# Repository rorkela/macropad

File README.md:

# EE2504: Hybrid Macropad (Wired + Dongle)

## Team

| Name | Roll Number |
|---|---|
| Sarthak Kumar Mishra |EE24BTECH11221|
| Naman Singh |EE24BTECH11216|
| Dhawal Saini |EE24BTECH11015|
| Sidharth V |EE24BTECH11224|
| Vantaku Sai Yashwant |EE24BTECH11225|
| Sriram Nulu |EE24BTECH11217|

## Details
- 2 Layer PCB for Macropad+Dongle Pair
- STM32F103C8T6 Based
- Programmed with `libopencm3`
- ssd1306 display integrated
- CAD Model designed to be 3D Printed for keycaps, encoder caps and casing.
- `microui` based key-map programming interface

## Instruction
1. Make the libraries (`libopencm3`)
2. Make and flash bootloader using `make flash`
3. Make and flash macropad firmware using `make flash` or the dfu script
4. Generate keymaps and flash using `mapping_gen`
# Current Status
- [x] PCB Ordered
## Wired
- [x] Bootloader Firmware
- [x] USB HID Firmware
- [x] DFU Firmware
- [x] Encoder Firmware
- [x] Display Firmware
- [x] All module integration
- [x] Multi key mapping
- [ ] Multi key sequential mapping

## Wireless
- [x] Dongle testing
- [x] nRF24L01 Firmware
- [ ] Battery Charging check
- [ ] Soldering SMD Mosfet + nRF modules
- [ ] Replacing PROG resistor for TP4056 module
- [ ] Complete Integration
## Other
- [x] Mapping generation and flashing with DFU
- [x] GUI
- [ ] Size Optimization for keymaps

## Images

## Links
- [CAD Model (Onshape)](https://cad.onshape.com/documents/8695aacad1c4b6aaf32709eb/w/c4719be3eaa84105acadf71a/e/89d918a88e3d346d4846fa41)

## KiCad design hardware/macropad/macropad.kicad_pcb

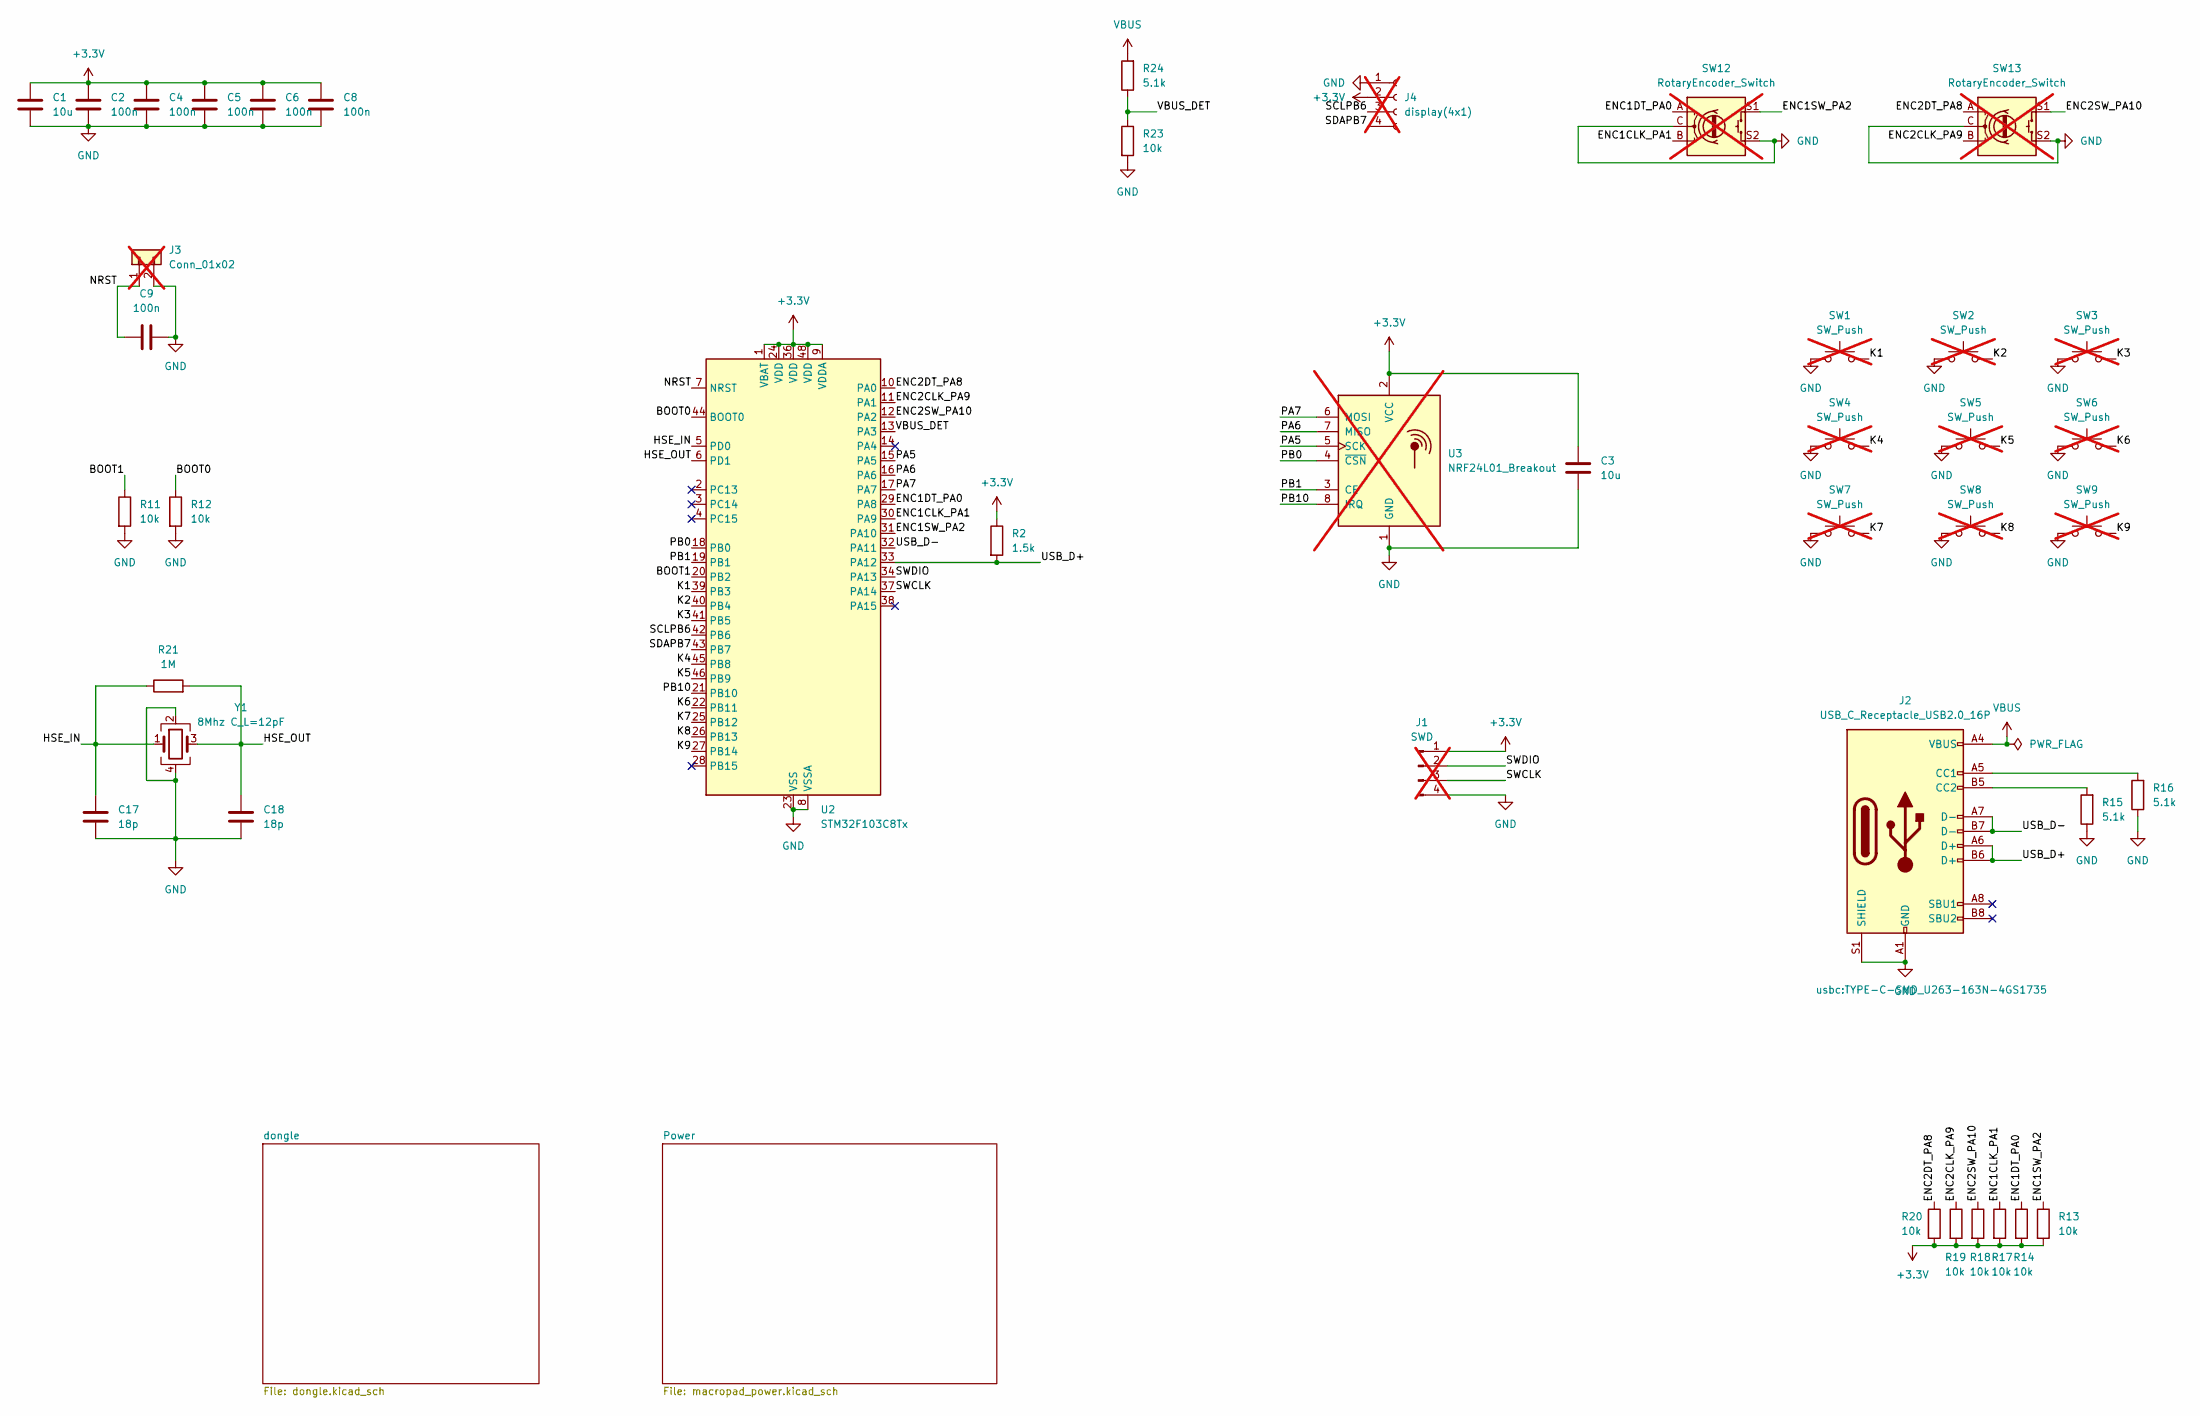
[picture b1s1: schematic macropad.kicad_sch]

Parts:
C1, C3: 10u; C_0805_2012Metric
C2, C4, C5, C6, C8, C9: 100n; C_0603_1608Metric
C17: 18p; C_0201_0603Metric
C18: 18p; C_0201_0603Metric; MPN GCM0335C1H180FA16D
J1: SWD; PinHeader_1x04_P2.54mm_Vertical; not fitted
J2: USB_C_Receptacle_USB2.0_16P; TYPE-C-SMD_U263-163N-4GS1735; MPN U263-163N-4WS1735-XKB-5A
J3: Conn_01x02; Hirose_DF13-02P-1.25DSA_1x02_P1.25mm_Vertical; not fitted
J4: display(4x1); PinHeader_1x04_P2.54mm_Vertical; not fitted
R2: 1.5k; R_0603_1608Metric
R11, R12, R14, R17, R18, R19, R20, R23: 10k; R_0805_2012Metric
R13: 10k; R_0805_2012Metric; MPN RC0805JR-0710KL
R15: 5.1k; R_0603_1608Metric; MPN RT0603FRE075K1L
R16, R24: 5.1k; R_0603_1608Metric
R21: 1M; R_0603_1608Metric
SW1, SW2, SW3, SW4, SW5, SW6, SW7, SW8, SW9: SW_Push; Kailh_socket_MX; not fitted
SW12: RotaryEncoder_Switch; RotaryEncoder_Alps_EC12E-Switch_Vertical_H20mm; MPN KY-040; not fitted
SW13: RotaryEncoder_Switch; RotaryEncoder_Alps_EC12E-Switch_Vertical_H20mm; not fitted
U2: STM32F103C8Tx; LQFP-48_7x7mm_P0.5mm; MPN STM32F103C8T6
U3: NRF24L01_Breakout; nRF24L01_Breakout; not fitted
Y1: 8Mhz C_L=12pF; Crystal_SMD_3225-4Pin_3.2x2.5mm; MPN X32258MOB4SI

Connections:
+3.3V: C1.1, C2.1, C3.1, C4.1, C5.1, C6.1, C8.1, J1.1, J4.2, R2.1, R13.2, R14.2, R17.2, R18.2, R19.2, R20.2, U2.1 (VBAT), U2.9 (VDDA), U2.24 (VDD), U2.36 (VDD), U2.48 (VDD), U3.2 (VCC); also elsewhere on the board
/BOOT0: R12.1, U2.44 (BOOT0)
/BOOT1: R11.1, U2.20 (PB2)
/ENC1CLK_PA1: R17.1, SW12.B, U2.30 (PA9)
/ENC1DT_PA0: R14.1, SW12.A, U2.29 (PA8)
/ENC1SW_PA2: R13.1, SW12.S1, U2.31 (PA10)
/ENC2CLK_PA9: R19.1, SW13.B, U2.11 (PA1)
/ENC2DT_PA8: R20.1, SW13.A, U2.10 (PA0)
/ENC2SW_PA10: R18.1, SW13.S1, U2.12 (PA2)
/HSE_IN: C17.1, R21.1, U2.5 (PD0), Y1.1
/HSE_OUT: C18.1, R21.2, U2.6 (PD1), Y1.3
/K1: SW1.2, U2.39 (PB3)
/K2: SW2.2, U2.40 (PB4)
/K3: SW3.2, U2.41 (PB5)
/K4: SW4.2, U2.45 (PB8)
/K5: SW5.2, U2.46 (PB9)
/K6: SW6.2, U2.22 (PB11)
/K7: SW7.2, U2.25 (PB12)
/K8: SW8.2, U2.26 (PB13)
/K9: SW9.2, U2.27 (PB14)
/NRST: C9.2, J3.1, U2.7 (NRST)
/PA5: U2.15 (PA5), U3.5 (SCK)
/PA6: U2.16 (PA6), U3.7 (MISO)
/PA7: U2.17 (PA7), U3.6 (MOSI)
/PB0: U2.18 (PB0), U3.4 (~CSN)
/PB1: U2.19 (PB1), U3.3 (CE)
/PB10: U2.21 (PB10), U3.8 (IRQ)
/SCLPB6: J4.3, U2.42 (PB6)
/SDAPB7: J4.4, U2.43 (PB7)
/SWCLK: J1.3, U2.37 (PA14)
/SWDIO: J1.2, U2.34 (PA13)
/USB_D+: J2.A6 (D+), J2.B6 (D+), R2.2, U2.33 (PA12)
/USB_D-: J2.A7 (D-), J2.B7 (D-), U2.32 (PA11)
/VBUS_DET: R23.1, R24.1, U2.13 (PA3)
GND: C1.2, C2.2, C3.2, C4.2, C5.2, C6.2, C8.2, C9.1, C17.2, C18.2, J1.4, J2.A1 (GND), J2.A12 (GND), J2.B1 (GND), J2.B12 (GND), J2.S1 (SHIELD), J3.2, J4.1, R11.2, R12.2, R15.1, R16.1, R23.2, SW1.1, SW2.1, SW3.1, SW4.1, SW5.1, SW6.1, SW7.1, SW8.1, SW9.1, SW12.C, SW12.S2, SW13.C, SW13.S2, U2.8 (VSSA), U2.23 (VSS), U2.35 (VSS), U2.47 (VSS), U3.1 (GND), Y1.2, Y1.4; also elsewhere on the board
unnamed: J2.A5 (CC1), R16.2
unnamed: J2.B5 (CC2), R15.2
VBUS: J2.A4 (VBUS), J2.A9 (VBUS), J2.B4 (VBUS), J2.B9 (VBUS), R24.2; also elsewhere on the board

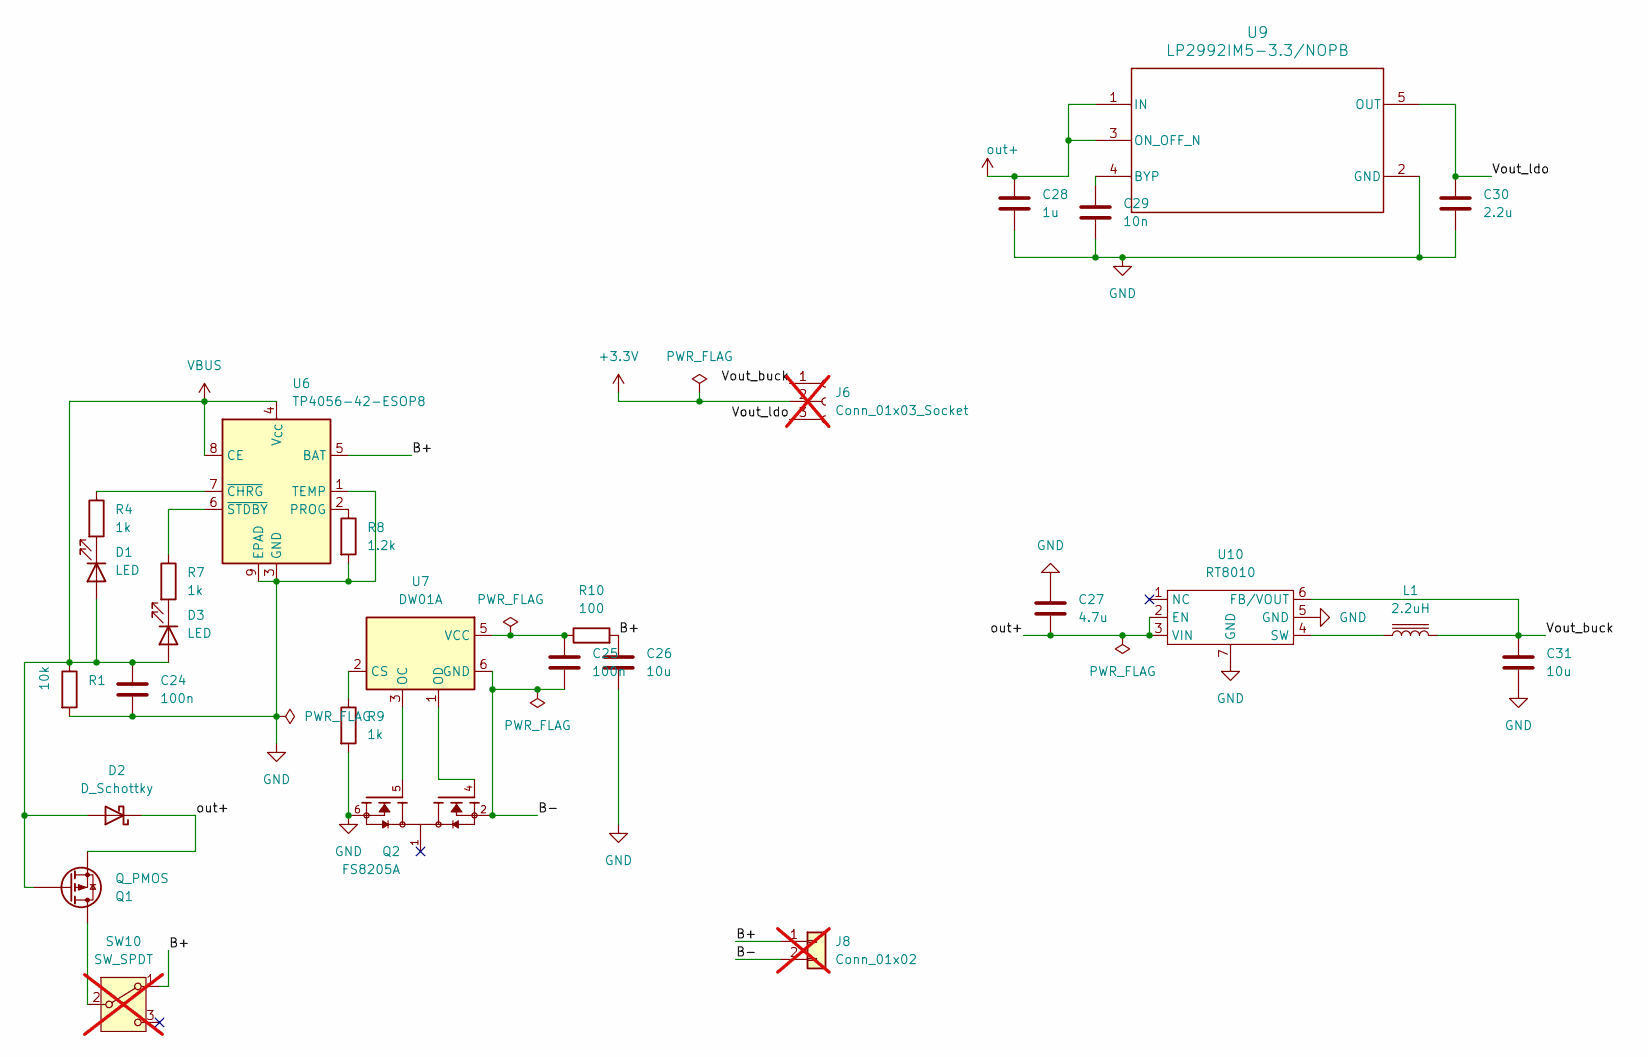
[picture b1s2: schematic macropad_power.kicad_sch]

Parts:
C24: 100n; C_0603_1608Metric; MPN AC0603JRX7R9BB104
C25: 100n; C_0603_1608Metric
C26: 10u; C_0805_2012Metric; MPN GRT21BR61C106KE01L
C27: 4.7u; C_0603_1608Metric; MPN GRM188Z71C475KE21D
C28: 1u; C_0805_2012Metric
C29: 10n; C_0603_1608Metric
C30: 2.2u; C_0603_1608Metric; MPN TMK107BBJ225KAHT
C31: 10u; C_0805_2012Metric
D1: LED; LED_0805_2012Metric
D2: D_Schottky; D_SMA; MPN SS34
D3: LED; LED_0805_2012Metric; MPN 17-21SURC/S530-A3/4T
J6: Conn_01x03_Socket; Hirose_DF13-03P-1.25DSA_1x03_P1.25mm_Vertical; not fitted
J8: Conn_01x02; SolderWire-0.5sqmm_1x02_P4.6mm_D0.9mm_OD2.1mm; not fitted
L1: 2.2uH; L_10.4x10.4_H4.8; MPN CDRH104R 2.2uH
Q1: Q_PMOS; SOT-23-3; MPN SI2305CDS-T1-GE3
Q2: FS8205A; SOP65P640X120-8N; PARTREV 1.7
R1: 10k; R_0805_2012Metric
R4, R7: 1k; R_0603_1608Metric
R8: 1.2k; R_0603_1608Metric; MPN AC0603FR-071K2L
R9: 1k; R_0603_1608Metric; MPN AC0603FR-071KL
R10: 100; R_0201_0603Metric; MPN AC0201FR-07100RL
SW10: SW_SPDT; SS12F23L5 spdt; not fitted
U6: TP4056-42-ESOP8; SOIC-8-1EP_3.9x4.9mm_P1.27mm_EP2.41x3.3mm_ThermalVias; MPN TP4056
U7: DW01A; SOT-23-6; MPN DW01A
U9: LP2992IM5-3.3/NOPB; DBV0005A_N; MPN LP2992IM5-3.3/NOPB
U10: RT8010; WDFN-6L; MPN RT8010-33GQW

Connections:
+3.3V: J6.2; also elsewhere on the board
/Power/B+: C26.1, J8.1, R10.2, SW10.1 (A), U6.5 (BAT)
/Power/B-: C25.2, J8.2, Q2.2, Q2.3, U7.6 (GND)
/Power/Vout_buck: C31.1, J6.1, L1.2, U10.6 (FB/VOUT)
/Power/Vout_ldo: C30.1, J6.3, U9.5 (OUT)
GND: C24.2, C26.2, C27.1, C28.2, C29.2, C30.2, C31.2, Q2.6, Q2.7, R1.2, R8.2, R9.2, U6.1 (TEMP), U6.3 (GND), U6.9 (EPAD), U9.2 (GND), U10.5 (GND), U10.7 (GND); also elsewhere on the board
unnamed: D1.1 (K), R4.2
unnamed: D3.1 (K), R7.2
unnamed: Q1.3 (D), SW10.2 (B)
unnamed: R8.1, U6.2 (PROG)
unnamed: R4.1, U6.7 (~CHRG)
unnamed: R7.1, U6.6 (~STDBY)
unnamed: R9.1, U7.2 (CS)
unnamed: Q2.5, U7.3 (OC)
unnamed: Q2.4, U7.1 (OD)
unnamed: C25.1, R10.1, U7.5 (VCC)
unnamed: C29.1, U9.4 (BYP)
unnamed: L1.1, U10.4 (SW)
VBUS: C24.1, D1.2 (A), D2.2 (A), D3.2 (A), Q1.1 (G), R1.1, U6.4 (V_{CC}), U6.8 (CE); also elsewhere on the board
out+: C27.2, C28.1, D2.1 (K), Q1.2 (S), U9.1 (IN), U9.3 (ON_OFF_N), U10.2 (EN), U10.3 (VIN)

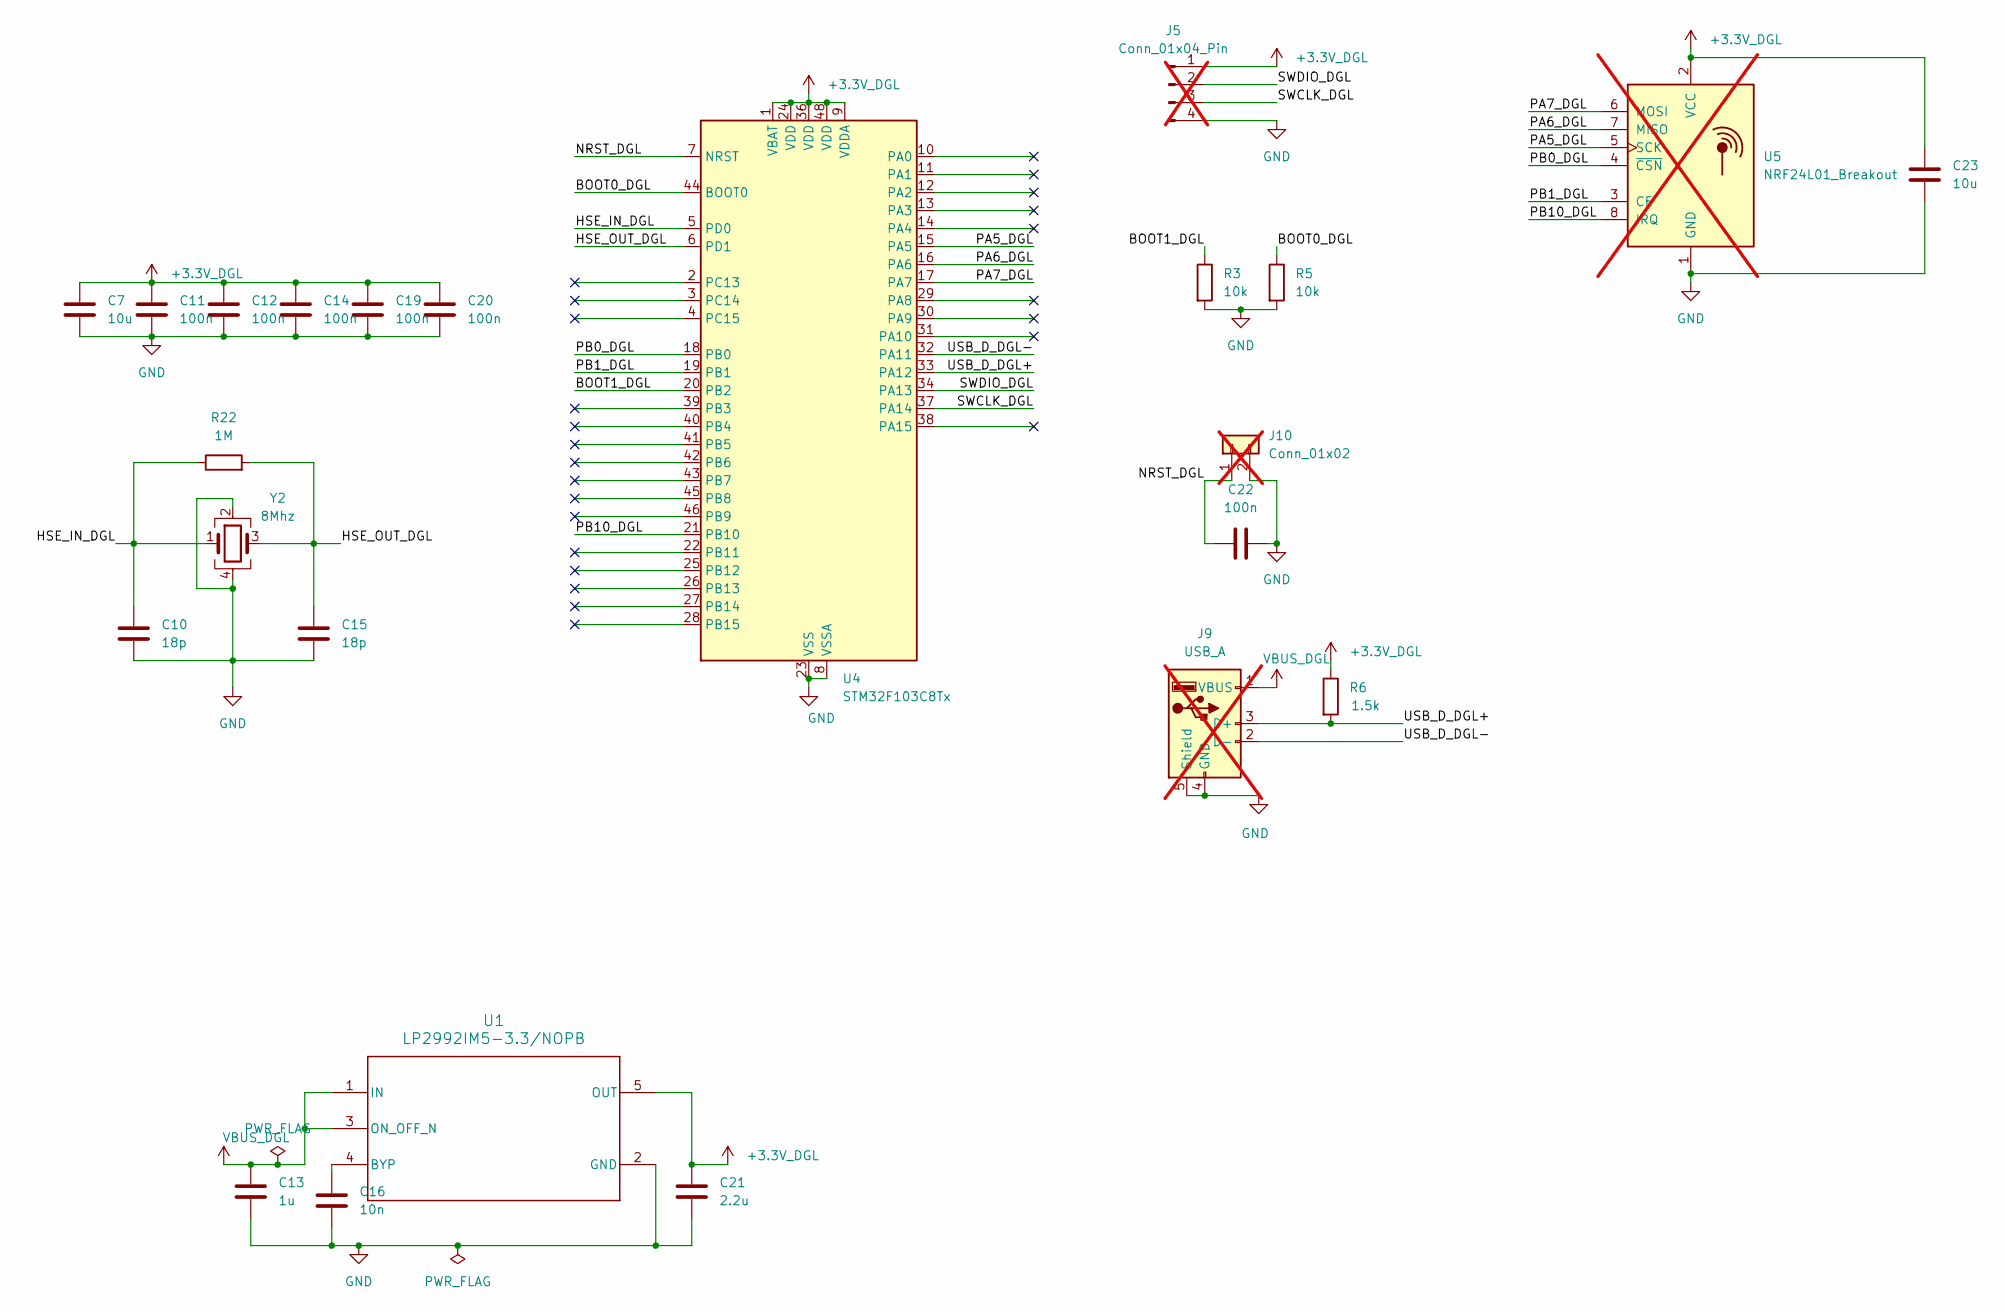
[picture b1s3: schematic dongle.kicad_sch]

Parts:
C7, C23: 10u; C_0805_2012Metric
C10, C15: 18p; C_0201_0603Metric
C11, C12, C14, C19, C20, C22: 100n; C_0603_1608Metric
C13: 1u; C_0805_2012Metric; MPN UMK212B7105KGHT
C16: 10n; C_0603_1608Metric
C21: 2.2u; C_0603_1608Metric
J5: Conn_01x04_Pin; PinHeader_1x04_P2.54mm_Horizontal; not fitted
J9: USB_A; U-G-O4DD-W-1; not fitted
J10: Conn_01x02; Hirose_DF13-02P-1.25DSA_1x02_P1.25mm_Vertical; not fitted
R3, R5: 10k; R_0805_2012Metric
R6: 1.5k; R_0603_1608Metric; MPN RT0603FRE071K5L
R22: 1M; R_0603_1608Metric; MPN CRCW06031M00FKEA
U1: LP2992IM5-3.3/NOPB; DBV0005A_N
U4: STM32F103C8Tx; LQFP-48_7x7mm_P0.5mm
U5: NRF24L01_Breakout; nRF24L01_Breakout; not fitted
Y2: 8Mhz; Crystal_SMD_3225-4Pin_3.2x2.5mm; MPN X32258MOB4SI

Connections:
+3.3V_DGL: C7.1, C11.1, C12.1, C14.1, C19.1, C20.1, C21.1, C23.1, J5.1, R6.1, U1.5 (OUT), U4.1 (VBAT), U4.9 (VDDA), U4.24 (VDD), U4.36 (VDD), U4.48 (VDD), U5.2 (VCC)
/dongle/BOOT0_DGL: R5.1, U4.44 (BOOT0)
/dongle/BOOT1_DGL: R3.1, U4.20 (PB2)
/dongle/HSE_IN_DGL: C10.1, R22.1, U4.5 (PD0), Y2.1
/dongle/HSE_OUT_DGL: C15.1, R22.2, U4.6 (PD1), Y2.3
/dongle/NRST_DGL: C22.2, J10.1, U4.7 (NRST)
/dongle/PA5_DGL: U4.15 (PA5), U5.5 (SCK)
/dongle/PA6_DGL: U4.16 (PA6), U5.7 (MISO)
/dongle/PA7_DGL: U4.17 (PA7), U5.6 (MOSI)
/dongle/PB0_DGL: U4.18 (PB0), U5.4 (~CSN)
/dongle/PB1_DGL: U4.19 (PB1), U5.3 (CE)
/dongle/PB10_DGL: U4.21 (PB10), U5.8 (IRQ)
/dongle/SWCLK_DGL: J5.3, U4.37 (PA14)
/dongle/SWDIO_DGL: J5.2, U4.34 (PA13)
/dongle/USB_D_DGL+: J9.3 (D+), R6.2, U4.33 (PA12)
/dongle/USB_D_DGL-: J9.2 (D-), U4.32 (PA11)
GND: C7.2, C10.2, C11.2, C12.2, C13.2, C14.2, C15.2, C16.2, C19.2, C20.2, C21.2, C22.1, C23.2, J5.4, J9.4 (GND), J9.5 (Shield), J10.2, R3.2, R5.2, U1.2 (GND), U4.8 (VSSA), U4.23 (VSS), U4.35 (VSS), U4.47 (VSS), U5.1 (GND), Y2.2, Y2.4; also elsewhere on the board
unnamed: C16.1, U1.4 (BYP)
VBUS_DGL: C13.1, J9.1 (VBUS), U1.1 (IN), U1.3 (ON_OFF_N)

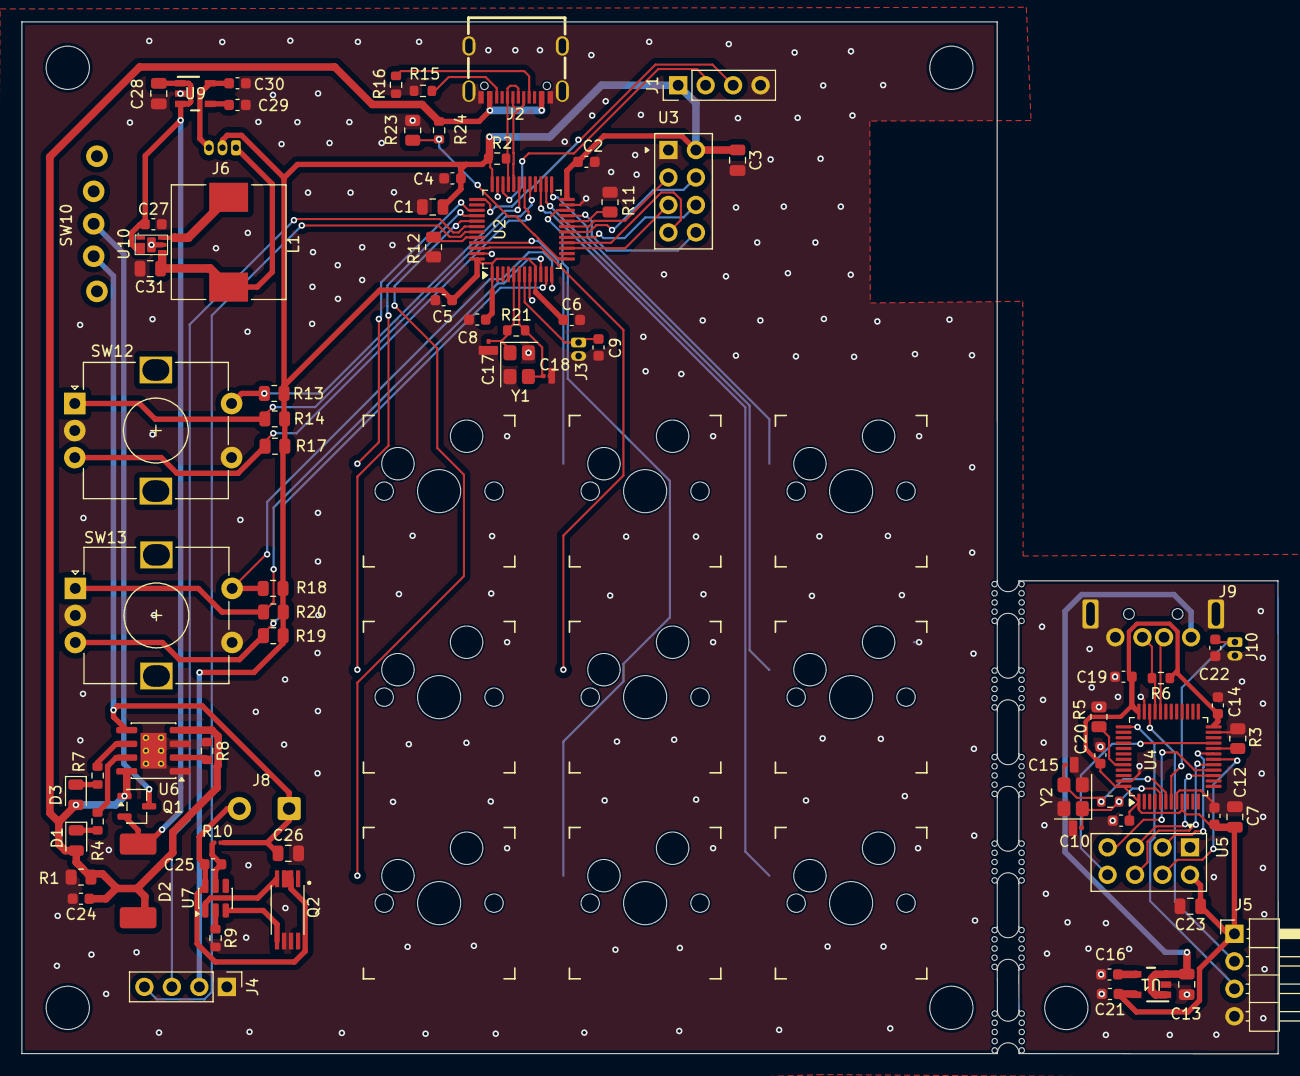
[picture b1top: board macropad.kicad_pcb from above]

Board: 2 copper layers, 116.1 x 95.4 mm, 93 parts (1 on the bottom side), 73 nets.

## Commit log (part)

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2026-02-18 init push
2026-02-25 push
2026-02-26 added some things like power
2026-02-26 peripherals connected passive,keys still to be done
2026-02-26 added firmware, gitignore; removed dongle kicad project
2026-02-26 removed .gitmodules
2026-02-26 switches added. folders deleted
2026-02-26 switches fixed
2026-02-26 added reset and 3x2 connector
2026-02-27 schema added for dongle. rearranged some parts
2026-02-27 schematic halfass done
2026-02-28 updated gitignore
2026-02-28 ERC satisfied. Net names changed for not global
2026-02-28 updated rules.mk
2026-02-28 added code for testing internal pullup
2026-02-28 removed keyswitch pullups
2026-02-28 switched to usb-c receptacle
2026-02-28 added new sch
2026-02-28 moved powering circuitry to new schematic
2026-02-28 captured TP4056 module
2026-02-28 captured the Buck(3_3V)
2026-03-01 added debouncing caps
2026-03-01 added 1k resistors to leds
2026-03-01 changed load capacitance, added oscillator for pad
2026-03-01 update oscillator + passives'
2026-03-01 something changed. i didnt track
2026-03-02 updated footprints
2026-03-03 replaced enc with module
2026-03-03 updated bat switch, added 10k resistors. fixed fps
2026-03-03 updated lp2992
2026-03-04 added usb-c receptacle footprint
2026-03-04 updated symbols. changed power. erc fixxed halfway
2026-03-05 erc for power checked
2026-03-05 erc for macropad checked
2026-03-05 updated symbols. all erc passed
2026-03-05 added usba fp, updated pcb, 5v to vbus
2026-03-06 replaced buttons with pads
2026-03-06 updated usb-c receptacle footprint
2026-03-11 updated. comments in whatsapp
2026-03-12 SS12F23L5 foorpting added
2026-03-12 updated pcb with switch
2026-03-12 pcb macropad done
2026-03-12 pcb done
2026-03-16 Updated Layout
2026-03-18 wrote code for testing i2c with ssd1306
2026-03-18 updated schematic and drc
2026-03-18 Macropad layout kinda done
2026-03-19 added drc
2026-03-19 routing
2026-03-19 rt8010 footprint
2026-03-19 rt8010 footprint+symbol done
2026-03-19 routing phase 2
2026-03-22 routing-macropad(67)
2026-03-26 updated dongle
2026-03-26 0-DRC
2026-03-29 0drc
2026-04-01 changes made
2026-04-01 schottkey updated and added mount hole
2026-04-02 added single pad usbc footprint
2026-04-02 added hole
2026-04-04 stitching done
2026-04-06 fab outputs
2026-04-07 wrote test code for nRF24L01
2026-04-08 proper fab outs
2026-04-08 fixed technical queries
2026-04-28 Add README.md for Hybrid Macropad project
2026-05-10 Updated BOM and Proposal
2026-06-04 Added complete test code to macropad.c
2026-06-05 Fixed test code
2026-06-19 Updated build system; Moved old code to tests
2026-06-25 Update project status and add 3D printing tasks
    Updated project status in the README with completed tasks and added new 3D printing tasks.
2026-06-25 Added Bootloader code
2026-06-25 Incomplete macropad code
2026-06-25 Hopefully working macropad code
2026-06-25 Added test mappings generation code
2026-06-25 Fixed bootloader dfu altsetting and mapping_gen keycodes
2026-06-27 incomplete display code. needs testing
2026-06-28 Added display code for debugging
2026-06-28 Added timekeeping; removed debouncing logic from systick
2026-06-29 Added display chunking and dirty bits
2026-06-29 added disp-layer call, keys not working
2026-06-29 Fixed
2026-06-30 Updated layer switching; added layer menu mode
2026-06-30 added IITH logo at start
